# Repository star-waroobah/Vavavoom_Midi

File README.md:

# Vavavoom: Custom USB-C MIDI Keypad

Vavavoom is a custom-designed USB-C MIDI keypad built for interactive music creation and Digital Audio Workstation (DAW) control. Designed entirely in KiCad, it puts music production hardware right at your fingertips using mechanical switches, a rotary encoder, and a custom capacitive touch strip. I made it as my Half-Life Week 3 project, to learn more about KiCad PCB design and to try out a capacitive touch strip.

## Features

* **Microcontroller:** Powered by the Waveshare ESP32-S3-Zero, which handles USB connectivity and processes user inputs.
* **Mechanical Switches:** 3 Kailh Choc mechanical switches for triggering notes or shortcuts.
* **Rotary Encoder:** An Alps EC11 encoder used for volume control, scrolling, or parameter adjustments.
* **Capacitive Touch Strip:** A custom 7-pad touch interface connected to the ESP32's touch pins to act as a pitch bend or mini touch keyboard.

## Schematic

## PCB

## 3D view

## Bill of Materials

| Designator | Footprint | Quantity | Value | Total Cost |
|------------|-----------|----------|-------|------------|
| D1, D2, D3 | LED_SK6812MINI-E_3.2x2.8mm_P1.5mm_ReverseMount | 3 | SK6812MINI-E | $3.36 |
| J1 | Capacitive Keys | 1 | Capacitive Touch Buttons | |
| RV1, RV2 | Potentiometer_Bourns_PTA1543_Single_Slide | 2 | Slider | $3.16 |
| SW1, SW2, SW3 | Kailh Choc Low-Profile Switches | 3 | SW_Push | $6.04 |
| SW4 | RotaryEncoder_Alps_EC11E-Switch_Vertical_H20mm | 1 | RotaryEncoder_Switch_MP | $1.44 |
| U1 | Waveshare ESP32-S3-Zero | 1 | Waveshare ESP32-S3-ZERO | $6.62 |

### Totals

| Vendor | Cost |
|--------|------|
| AliExpress | $19.59 |
| DigiKey | $12.35 |
| JLCPCB | $12.29 |
| **Total** | **$44.23** |

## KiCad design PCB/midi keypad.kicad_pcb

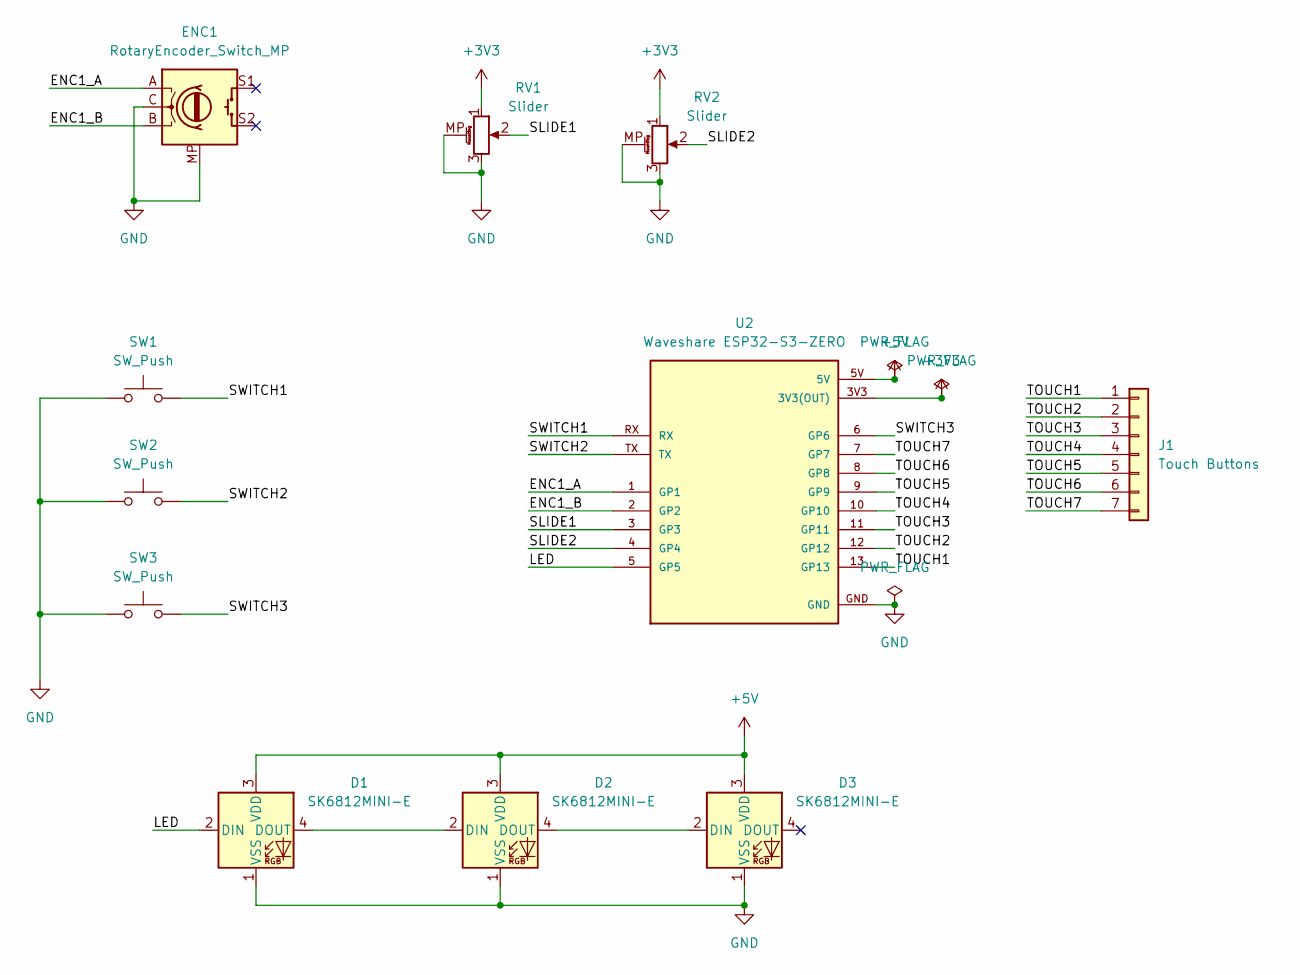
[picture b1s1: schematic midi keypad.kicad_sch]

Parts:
D1, D2, D3: SK6812MINI-E; LED_SK6812MINI-E_3.2x2.8mm_P1.5mm_ReverseMount
ENC1: RotaryEncoder_Switch_MP; RotaryEncoder_Alps_EC11E-Switch_Vertical_H20mm
J1: Touch Buttons; capacitive key
RV1, RV2: Slider; Potentiometer_Bourns_PTA1543_Single_Slide
SW1, SW2, SW3: SW_Push; Kailh Choc Low-Profile Switches
U2: Waveshare ESP32-S3-ZERO; Waveshare ESP32-S3-Zero; PARTREV NA

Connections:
+3V3: RV1.1, RV2.1, U2.3V3 (3V3(OUT))
+5V: D1.3 (VDD), D2.3 (VDD), D3.3 (VDD), U2.5V
/ENC1_A: ENC1.A, U2.1 (GP1)
/ENC1_B: ENC1.B, U2.2 (GP2)
/LED: D1.2 (DIN), U2.5 (GP5)
/SLIDE1: RV1.2, U2.3 (GP3)
/SLIDE2: RV2.2, U2.4 (GP4)
/SWITCH1: SW1.2, U2.RX
/SWITCH2: SW2.2, U2.TX
/SWITCH3: SW3.2, U2.6 (GP6)
/TOUCH1: J1.1, U2.13 (GP13)
/TOUCH2: J1.2, U2.12 (GP12)
/TOUCH3: J1.3, U2.11 (GP11)
/TOUCH4: J1.4, U2.10 (GP10)
/TOUCH5: J1.5, U2.9 (GP9)
/TOUCH6: J1.6, U2.8 (GP8)
/TOUCH7: J1.7, U2.7 (GP7)
GND: D1.1 (VSS), D2.1 (VSS), D3.1 (VSS), ENC1.C, ENC1.MP, RV1.3, RV1.MP (MountPin), RV2.3, RV2.MP (MountPin), SW1.1, SW2.1, SW3.1, U2.GND
unnamed: D1.4 (DOUT), D2.2 (DIN)
unnamed: D2.4 (DOUT), D3.2 (DIN)

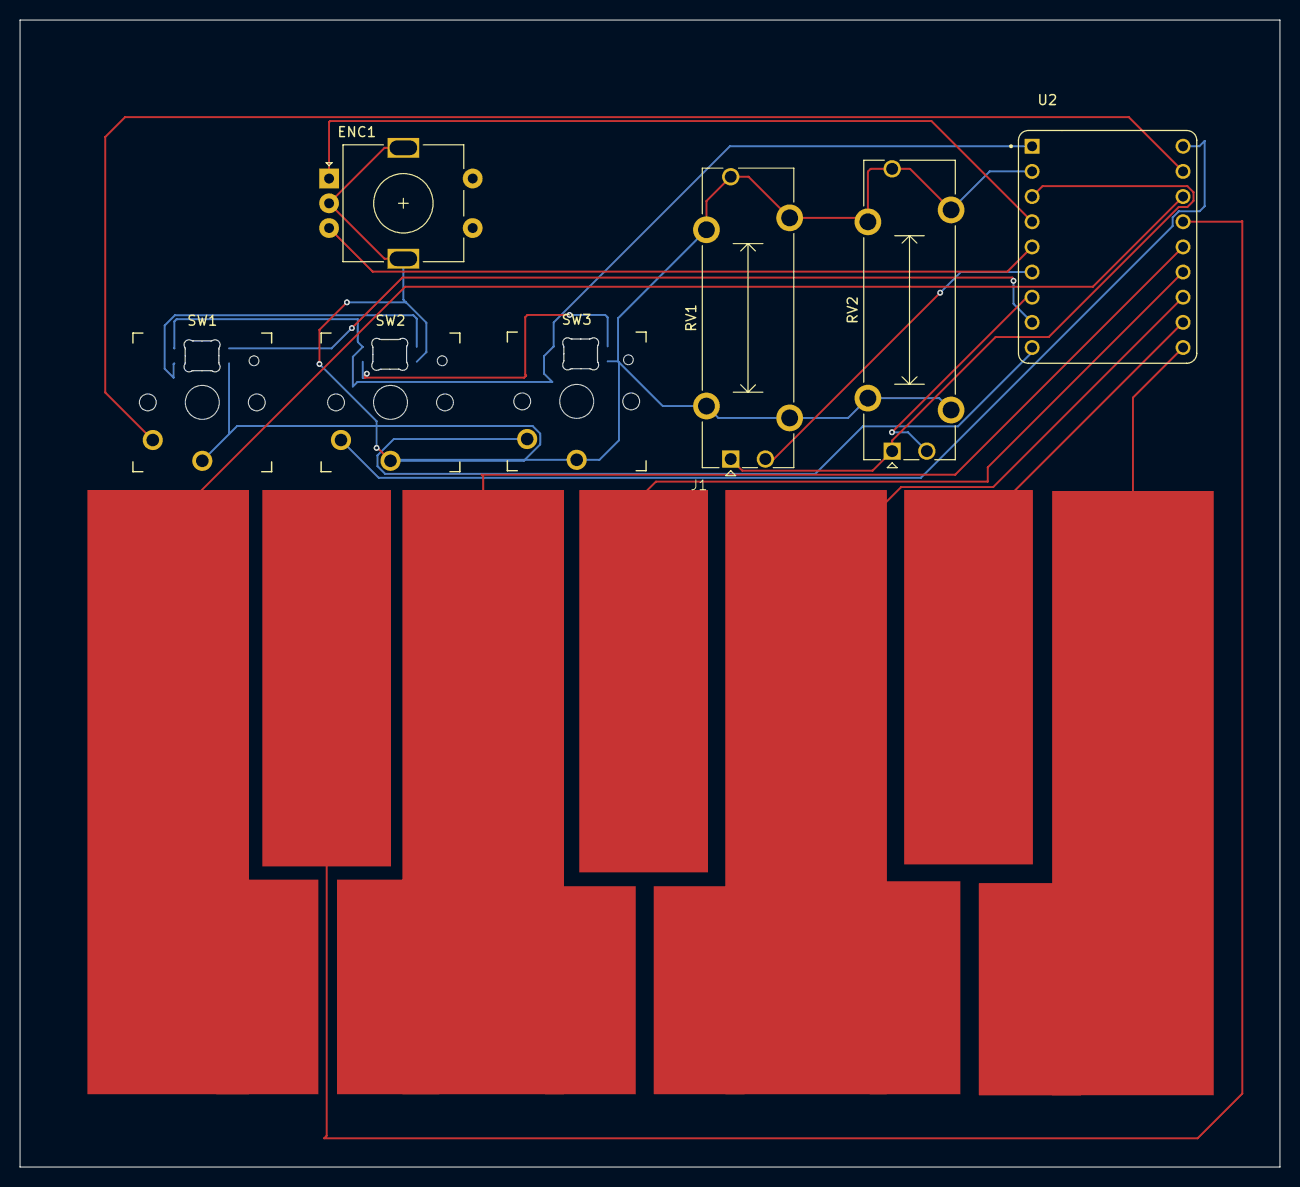
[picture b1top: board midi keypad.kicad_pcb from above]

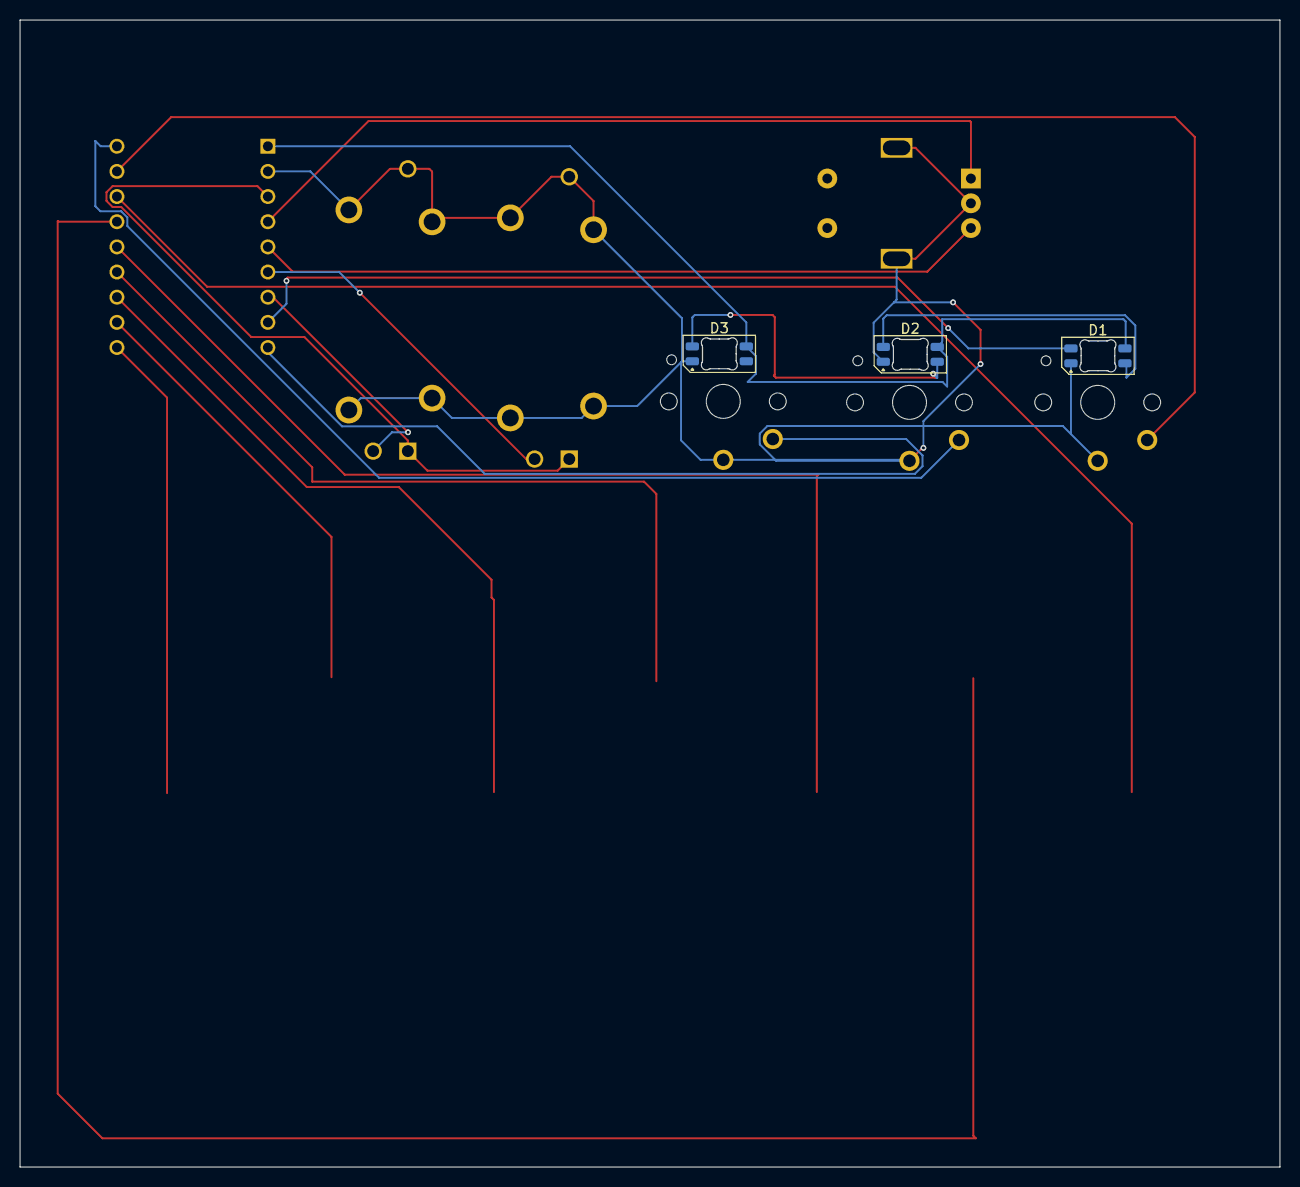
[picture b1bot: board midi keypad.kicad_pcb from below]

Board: 2 copper layers, 127.2 x 115.8 mm, 11 parts (3 on the bottom side), 20 nets.

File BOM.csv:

Item,Qty,Supplier,Cost/item,Total Cost,link
RotaryEncoder_Switch_MP,1,Aliexpress,$1.44,$1.44,https://www.aliexpress.us/item/3256807457768762.html
Waveshare ESP32-S3-ZERO,1,Aliexpress,$6.62,$6.62,https://www.aliexpress.com/item/1005007004089798.html
Capacitive touch keys,1,JLCPCB,$20.00,$20.00,https://jlcpcb.com/
SW_Push,2,aliepress,$2.01,$4.02,https://www.aliexpress.com/item/1005008883418065.html
Estimated total shipping,1,,,$0.00,
